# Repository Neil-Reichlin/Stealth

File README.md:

# Stealth
Stealth is a fully custom-built ergonomic split keyboard. This repository provides the adapted ZMK firmware.

## Usage 
ZMK provides US keycodes by default, and firmware/config is written in terms of them.
This keyboard's default layer instead uses the Swiss German character macros defined in
`include/locale/keys_de_swiss.h` (the `DE_*` codes below), which only produce the correct
character when **your OS's keyboard layout is set to Swiss German** - each macro sends the
raw physical-key code for wherever that character sits on a real Swiss keyboard, and it's
your OS's layout setting that turns that into the right character. If your OS is set to a
plain US layout instead, these keys will type their *US* character (e.g. `DE_MINUS` would
type `/` instead of `-`).

Note that `code_layer` and `bt_layer` in `stealth.keymap` currently use plain US `&kp` codes
(e.g. `&kp AT_SIGN`) rather than the `DE_*` macros, so those two layers assume a US layout and
won't produce the labeled character under a Swiss OS layout.

### Swiss character reference

Use these instead of the plain US `&kp` codes whenever you want the printed Swiss/German
character (with your OS set to a Swiss German layout). Full list in
[`include/locale/keys_de_swiss.h`](include/locale/keys_de_swiss.h).

| Character | ZMK code |
|---|---|
| `ä` | `DE_A_UMLAUT` |
| `ö` | `DE_O_UMLAUT` |
| `ü` | `DE_U_UMLAUT` |
| `à` | `DE_A_GRAVE` |
| `è` | `DE_E_GRAVE` |
| `é` | `DE_E_ACUTE` |
| `ç` | `DE_C_CEDILLA` |
| `¨` (diaeresis) | `DE_UMLAUT` |
| `´` (acute accent) | `DE_ACUTE` |
| `°` | `DE_DEGREE` / `DE_DEG` |
| `§` | `DE_SECTION` / `DE_SECT` |
| `€` | `DE_EURO` |
| `£` | `DE_POUND_SIGN` |
| `¢` | `DE_CENT` |
| `¦` | `DE_BROKEN_BAR` |
| `¬` | `DE_NOT` |
| `~` | `DE_TILDE` |
| `` ` `` | `DE_GRAVE` |
| `^` | `DE_CARET` |
| `\` | `DE_BACKSLASH` / `DE_BSLH` |
| `\|` | `DE_PIPE` |
| `[` | `DE_LEFT_BRACKET` / `DE_LBKT` |
| `]` | `DE_RIGHT_BRACKET` / `DE_RBKT` |
| `{` | `DE_LEFT_BRACE` / `DE_LBRC` |
| `}` | `DE_RIGHT_BRACE` / `DE_RBRC` |
| `@` | `DE_AT_SIGN` / `DE_AT` |
| `#` | `DE_HASH` / `DE_POUND` |
| `$` | `DE_DOLLAR` / `DE_DLLR` |
| `%` | `DE_PERCENT` / `DE_PRCNT` |
| `&` | `DE_AMPERSAND` / `DE_AMPS` |
| `*` | `DE_ASTERISK` / `DE_ASTRK` / `DE_STAR` |
| `+` | `DE_PLUS` |
| `-` | `DE_MINUS` |
| `_` | `DE_UNDERSCORE` / `DE_UNDER` |
| `=` | `DE_EQUAL` |
| `/` | `DE_SLASH` / `DE_FSLH` |
| `!` | `DE_EXCLAMATION` / `DE_EXCL` |
| `?` | `DE_QUESTION` / `DE_QMARK` |
| `"` | `DE_DOUBLE_QUOTES` / `DE_DQT` |
| `'` | `DE_SINGLE_QUOTE` / `DE_SQT` / `DE_APOS` |
| `,` | `DE_COMMA` |
| `.` | `DE_PERIOD` / `DE_DOT` |
| `:` | `DE_COLON` |
| `;` | `DE_SEMICOLON` / `DE_SEMI` |
| `<` | `DE_LESS_THAN` / `DE_LT` |
| `>` | `DE_GREATER_THAN` / `DE_GT` |
| `(` | `DE_LEFT_PARENTHESIS` / `DE_LPAR` |
| `)` | `DE_RIGHT_PARENTHESIS` / `DE_RPAR` |
| `0`-`9` | `DE_N0`-`DE_N9` |
| `a`-`z` | `DE_A`-`DE_Z` (note: `DE_Y`/`DE_Z` are swapped to match QWERTZ) |
| Space | `DE_SPACE` |

So for a backslash, use `&kp DE_BACKSLASH` (or the shorter alias `&kp DE_BSLH`) in place of
`&kp BSLH` - on a Swiss keyboard that's AltGr + the key next to left Shift, and `DE_BACKSLASH`
sends exactly that physical combination.

### Using these in ZMK Studio

You can't search for `DE_A_UMLAUT` (etc.) by name in Studio - these are C preprocessor macros
that get replaced with a raw keycode (plus an optional Shift/AltGr/Ctrl modifier) at compile
time, so by the time the firmware is running, the name is gone. Studio only ever sees "base
key + modifier," and displays the base key using its generic US name.

You can still build the identical binding by hand: in Studio, add a `Key Press` (`&kp`)
binding, pick the base key from the table below (shown by its Studio/US name), and toggle the
matching modifier next to it.

| Character | Base key in Studio | Modifier |
|---|---|---|
| `ä` | Apostrophe / Quote | none |
| `ö` | Semicolon / Colon | none |
| `ü` | Left Bracket | none |
| `à` | Apostrophe / Quote | Shift |
| `è` | Left Bracket | Shift |
| `é` | Semicolon / Colon | Shift |
| `ç` | 4 | Shift |
| `¨` (dead key) | Right Bracket | none |
| `´` (dead key) | Minus | AltGr |
| `°` | 4 | AltGr |
| `§` | Grave/Tilde (`` ` ``) | none |
| `€` | E | AltGr |
| `£` | Backslash/Pipe | Shift |
| `¢` | 8 | AltGr |
| `¦` | 1 | AltGr |
| `¬` | 6 | AltGr |
| `~` | Equal/Plus | AltGr |
| `` ` `` | Equal/Plus | Shift |
| `^` | Equal/Plus | none |
| `\` | Non-US Backslash/Pipe | AltGr |
| `\|` | 7 | AltGr |
| `[` | Left Bracket | AltGr |
| `]` | Right Bracket | AltGr |
| `{` | Apostrophe / Quote | AltGr |
| `}` | Backslash/Pipe | AltGr |
| `@` | 2 | AltGr |
| `#` | 3 | AltGr |
| `$` | Backslash/Pipe | none |
| `%` | 5 | Shift |
| `&` | 6 | Shift |
| `*` | 3 | Shift |
| `+` | 1 | Shift |
| `-` | Slash | none |
| `_` | Slash | Shift |
| `=` | 0 | Shift |
| `/` | 7 | Shift |
| `!` | Right Bracket | Shift |
| `?` | Minus | Shift |
| `"` | 2 | Shift |
| `'` | Minus | none |
| `,` | Comma | none |
| `.` | Period | none |
| `:` | Period | Shift |
| `;` | Comma | Shift |
| `<` | Non-US Backslash/Pipe | none |
| `>` | Non-US Backslash/Pipe | Shift |
| `(` | 8 | Shift |
| `)` | 9 | Shift |
| `y` | physical key **Z** | none |
| `z` | physical key **Y** | none |

Letters other than `y`/`z` and digits `0`-`9` map 1:1 to the same-named US key, no modifier.

## Flashing

Every push builds both halves' firmware via GitHub Actions. Open the latest
run under the *Actions* tab, download the `firmware` artifact, and unzip it -
you'll get one `.uf2` file per shield (`stealth_left-nice_nano__zmk-zmk.uf2`
and `stealth_right-nice_nano__zmk-zmk.uf2`).

To flash a half: double-tap its reset button to put it into bootloader mode
(it shows up as a USB drive named `NICENANO`), then drag the matching
`.uf2` file onto that drive. It flashes and reboots automatically.

## Editing the layout live with ZMK Studio

The left/central half is built with [ZMK Studio](https://zmk.studio) support,
so you can remap keys without rebuilding or reflashing firmware:

1. Flash the current firmware to both halves (see above) at least once -
   Studio only changes the keymap that's already on the device, it doesn't
   install new firmware.
2. Connect the **left** half to your computer with a USB cable (the right
   half doesn't need Studio and isn't reachable this way).
3. Open [studio.zmk.dev](https://studio.zmk.dev) in Chrome (or the ZMK
   Studio desktop app) and connect to the keyboard - it should be detected
   automatically over the USB serial connection.
4. Edit key bindings, layers, etc. in the visual editor. Changes are pushed
   to the keyboard live and are saved to flash, so they persist across
   power cycles - no rebuild/reflash needed.

Changes made in Studio live only on the physical keyboard, not in this repo.
If you want a change to stick around permanently (e.g. survive a factory
reset, or apply after reflashing from a fresh build), port it back into
`boards/shields/stealth/stealth.keymap` by hand.

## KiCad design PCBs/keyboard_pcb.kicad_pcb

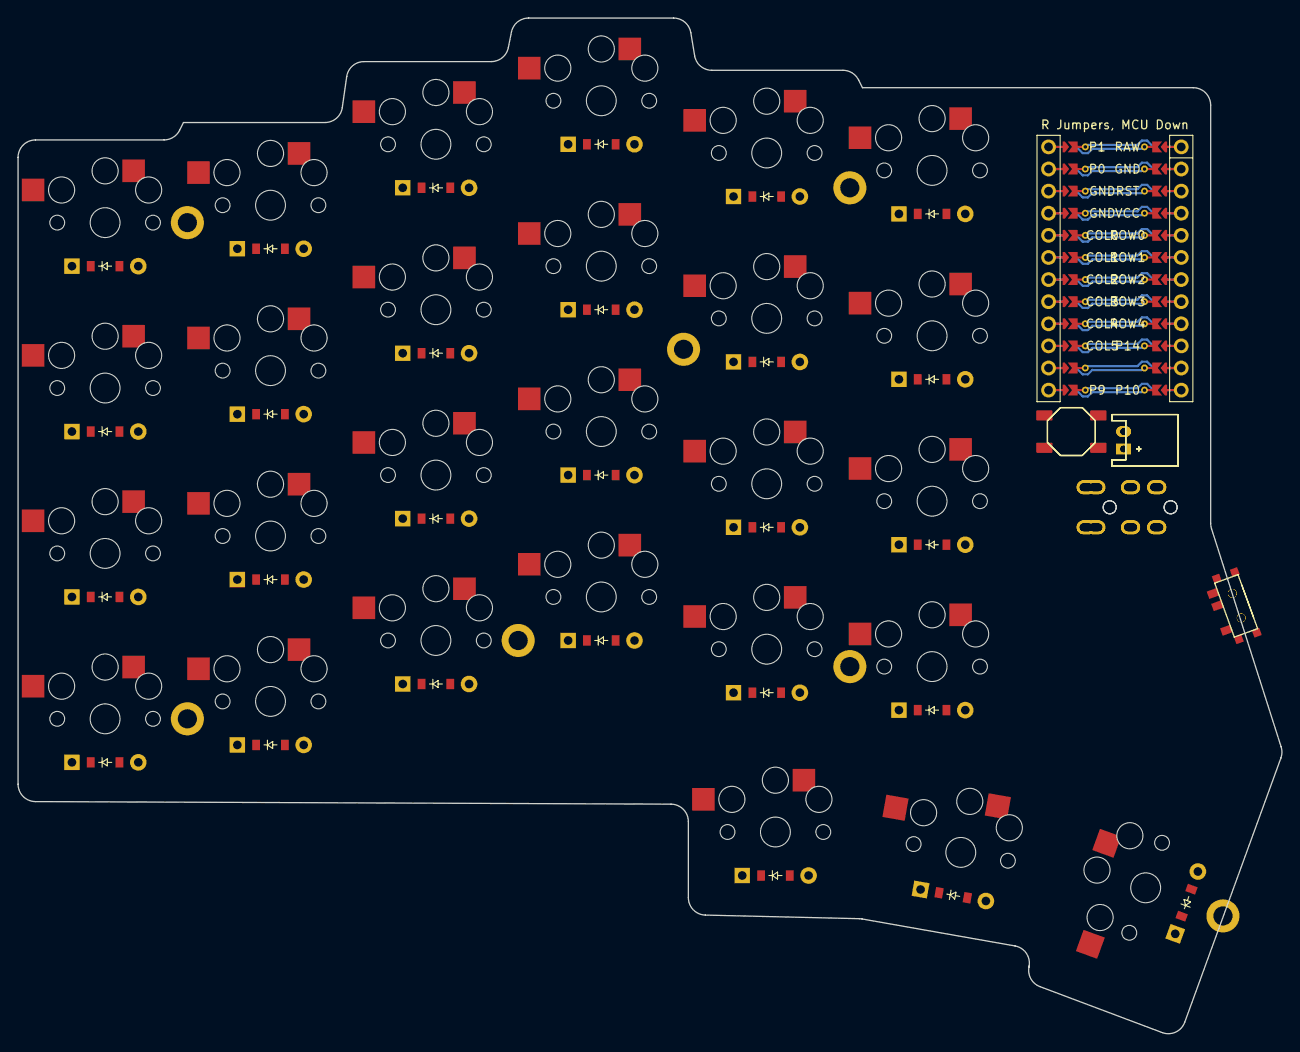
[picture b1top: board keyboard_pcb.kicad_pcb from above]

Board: 2 copper layers, 145.2 x 116.7 mm, 70 parts (0 on the bottom side), 43 nets.

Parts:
B1, B2: SW_TACT_ALPS_SKQGABE010
D1, D2, D3, D4, D5, D6, D7, D8, D9, D10, D11, D12, D13, D14, D15, D16, D17, D18, D19, D20, D21, D22, D23, D24, D25, D26, D27: ComboDiode
H1, H2, H3, H4, H5, H6, H7: mounting_hole_plated
JST1, JST2: JST_PH_S2B-PH-K_02x2.00mm_Angled
MCU1: mcu_nice_nano
S1, S2, S3, S4, S5, S6, S7, S8, S9, S10, S11, S12, S13, S14, S15, S16, S17, S18, S19, S20, S21, S22, S23, S24, S25, S26, S27: PG1350
T1, T2: SPDT_C128955
TRRS1, TRRS2: TRRS-PJ-320A-dual

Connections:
COL0: MCU1.105, S1.1, S2.1, S3.1, S4.1
COL1: MCU1.106, S5.1, S6.1, S7.1, S8.1
COL2: MCU1.107, S9.1, S10.1, S11.1, S12.1
COL3: MCU1.108, S13.1, S14.1, S15.1, S16.1, S25.1
COL4: MCU1.109, S17.1, S18.1, S19.1, S20.1, S26.1
COL5: MCU1.110, S21.1, S22.1, S23.1, S24.1, S27.1
GND: B1.1, B2.1, JST1.2, JST2.2, MCU1.103, MCU1.104, MCU1.123, T1.2, T2.2, TRRS1.2, TRRS2.2
P0: MCU1.102, TRRS1.4, TRRS2.4
P1: MCU1.101, TRRS1.3, TRRS2.3
ROW0: D25.1, D26.1, D27.1, MCU1.120
ROW1: D4.1, D8.1, D12.1, D16.1, D20.1, D24.1, MCU1.119
ROW2: D3.1, D7.1, D11.1, D15.1, D19.1, D23.1, MCU1.118
ROW3: D2.1, D6.1, D10.1, D14.1, D18.1, D22.1, MCU1.117
ROW4: D1.1, D5.1, D9.1, D13.1, D17.1, D21.1, MCU1.116
RST: B1.2, B2.2, MCU1.122
VCC: JST1.1, JST2.1, MCU1.121, T1.1, T2.1, TRRS1.1, TRRS2.1
far_thumb: D27.2, S27.2
home_thumb: D26.2, S26.2
index_bottom: D17.2, S17.2
index_home: D18.2, S18.2
index_num: D19.2, S19.2
index_top: D20.2, S20.2
inner_bottom: D21.2, S21.2
inner_home: D22.2, S22.2
inner_num: D23.2, S23.2
inner_top: D24.2, S24.2
middle_bottom: D13.2, S13.2
middle_home: D14.2, S14.2
middle_num: D15.2, S15.2
middle_top: D16.2, S16.2
near_thumb: D25.2, S25.2
pinky_bottom: D1.2, S1.2
pinky_home: D2.2, S2.2
pinky_num: D3.2, S3.2
pinky_top: D4.2, S4.2
ring_bottom: D9.2, S9.2
ring_home: D10.2, S10.2
ring_num: D11.2, S11.2
ring_top: D12.2, S12.2
shift_bottom: D5.2, S5.2
shift_home: D6.2, S6.2
shift_num: D7.2, S7.2
shift_top: D8.2, S8.2

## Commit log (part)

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2024-11-11 Initial User Config.
2024-11-11 init
2024-11-13 default corne structure
2024-11-13 new folder
2024-11-13 lsls
2024-11-13 added config to root
2024-11-13 initial full setup
2024-11-13 fixed ;
2024-11-13 fixed >
2024-11-13 fixed §
2024-11-13 fixed character
2024-11-13 try23423424243
2024-11-14 test
2024-11-14 tsest
2024-11-14 keymap
2024-11-16 row2col
2024-11-16 isolate hardware
2024-11-17 refactor
2024-12-24 keymap update
2024-12-26 update code layer and add bluetooth layer
2024-12-28 custom shifts build test
2024-12-29 custom shift
2024-12-29 custom shifts swiss keyboard
2024-12-29 swiss shift
2024-12-29 swiss layout
2024-12-30 Update stealth.keymap, test german oe
2024-12-30 Update stealth.keymap, relative imports
2024-12-30 Update stealth.keymap, swiss locale
2024-12-30 Update stealth.keymap, added y to correct spot
2024-12-30 Update stealth.keymap, updated 0 key
2024-12-31 added hashtag and backslash, fixed underscore
2025-06-12 ergogen files added
2025-06-12 ergogen
2025-06-12 added gerbers
2025-06-16 pcbs
2026-01-07 build update
